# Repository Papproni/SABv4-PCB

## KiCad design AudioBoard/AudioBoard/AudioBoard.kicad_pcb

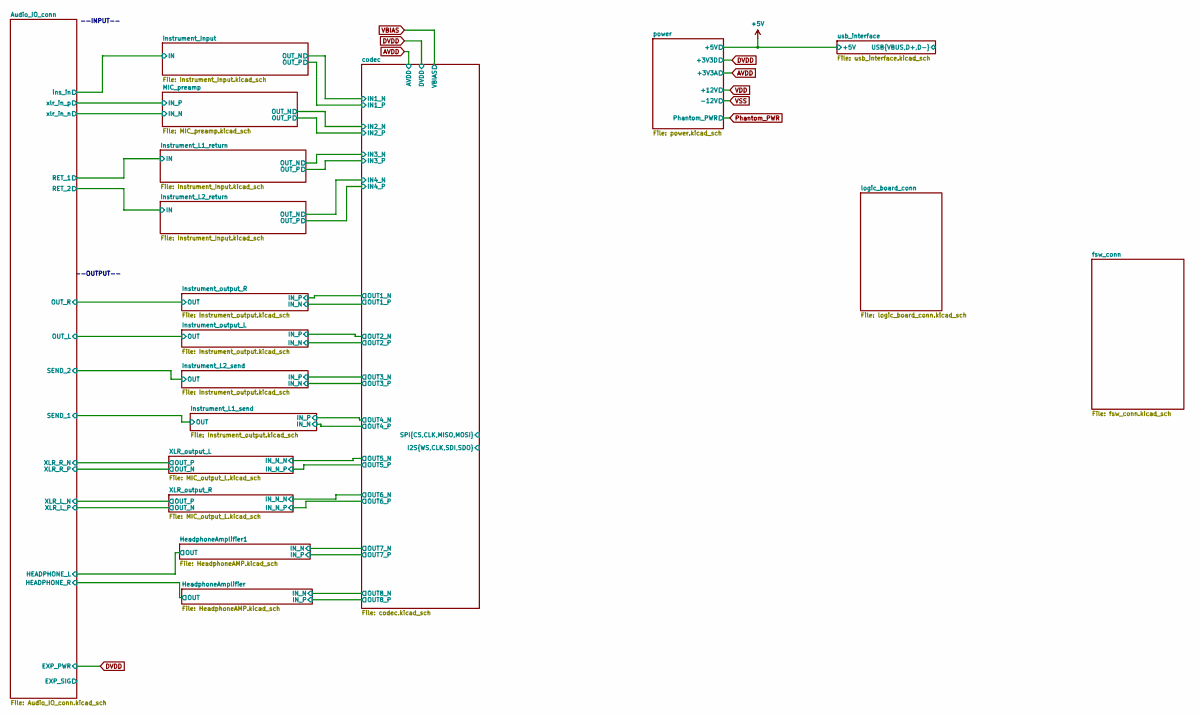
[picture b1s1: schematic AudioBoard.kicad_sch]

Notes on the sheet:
--OUTPUT--
--INPUT--

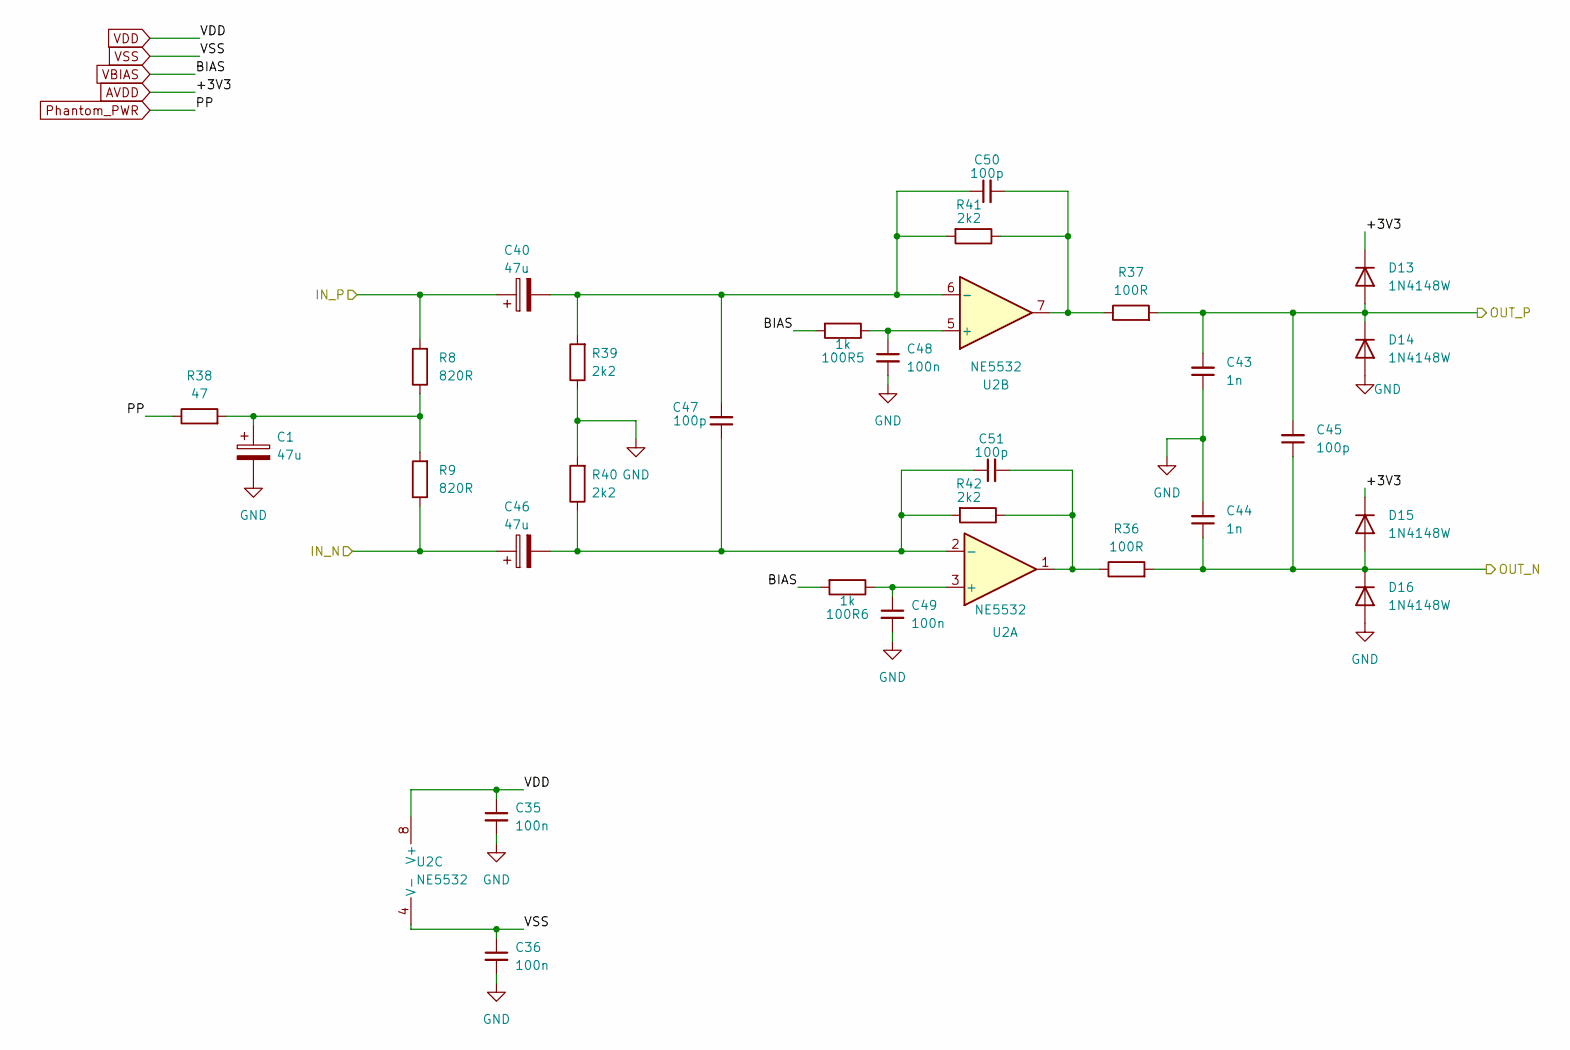
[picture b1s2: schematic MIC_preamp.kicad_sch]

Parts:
100R5, 100R6: 1k; R_0402_1005Metric; JLCPCB C11702
C1, C40, C46: 47u; CP_Radial_D6.3mm_P2.50mm; JLCPCB C45673
C35, C36, C48, C49: 100n; C_0402_1005Metric; JLCPCB C1591
C43, C44: 1n; C_0402_1005Metric; JLCPCB C1523
C45, C47, C50, C51: 100p; C_0402_1005Metric; JLCPCB C1546
D13, D14, D15, D16: 1N4148W; D_SOD-123; JLCPCB C81598
R8, R9: 820R; R_0603_1608Metric; JLCPCB C23253
R36, R37: 100R; R_0402_1005Metric; JLCPCB C25076
R38: 47; R_0603_1608Metric; JLCPCB C23182
R39, R40, R41, R42: 2k2; R_0402_1005Metric; JLCPCB C25879
U2: NE5532; SOIC-8_3.9x4.9mm_P1.27mm; JLCPCB C7426

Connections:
/Audio_IO_conn/xlr_in_n: C46.1, R9.1; also elsewhere on the board
/Audio_IO_conn/xlr_in_p: C40.1, R8.2; also elsewhere on the board
/MIC_preamp/OUT_N: C44.1, C45.1, D15.2 (A), D16.1 (K), R36.2; also elsewhere on the board
/MIC_preamp/OUT_P: C43.2, C45.2, D13.2 (A), D14.1 (K), R37.2; also elsewhere on the board
AVDD: D13.1 (K), D15.1 (K); also elsewhere on the board
GND: C1.2, C35.2, C36.2, C43.1, C44.2, C48.2, C49.2, D14.2 (A), D16.2 (A), R39.1, R40.2; also elsewhere on the board
unnamed: C1.1, R8.1, R9.2, R38.2
unnamed: C50.2, R37.1, R41.1, U2.7
unnamed: C51.2, R36.1, R42.1, U2.1
unnamed: 100R6.1, C49.1, U2.3 (+)
unnamed: C46.2, C47.1, C51.1, R40.1, R42.2, U2.2 (-)
unnamed: 100R5.1, C48.1, U2.5 (+)
unnamed: C40.2, C47.2, C50.1, R39.2, R41.2, U2.6 (-)
Phantom_PWR: R38.1; also elsewhere on the board
VBIAS: 100R5.2, 100R6.2; also elsewhere on the board
VDD: C35.1, U2.8 (V+); also elsewhere on the board
VSS: C36.1, U2.4 (V-); also elsewhere on the board

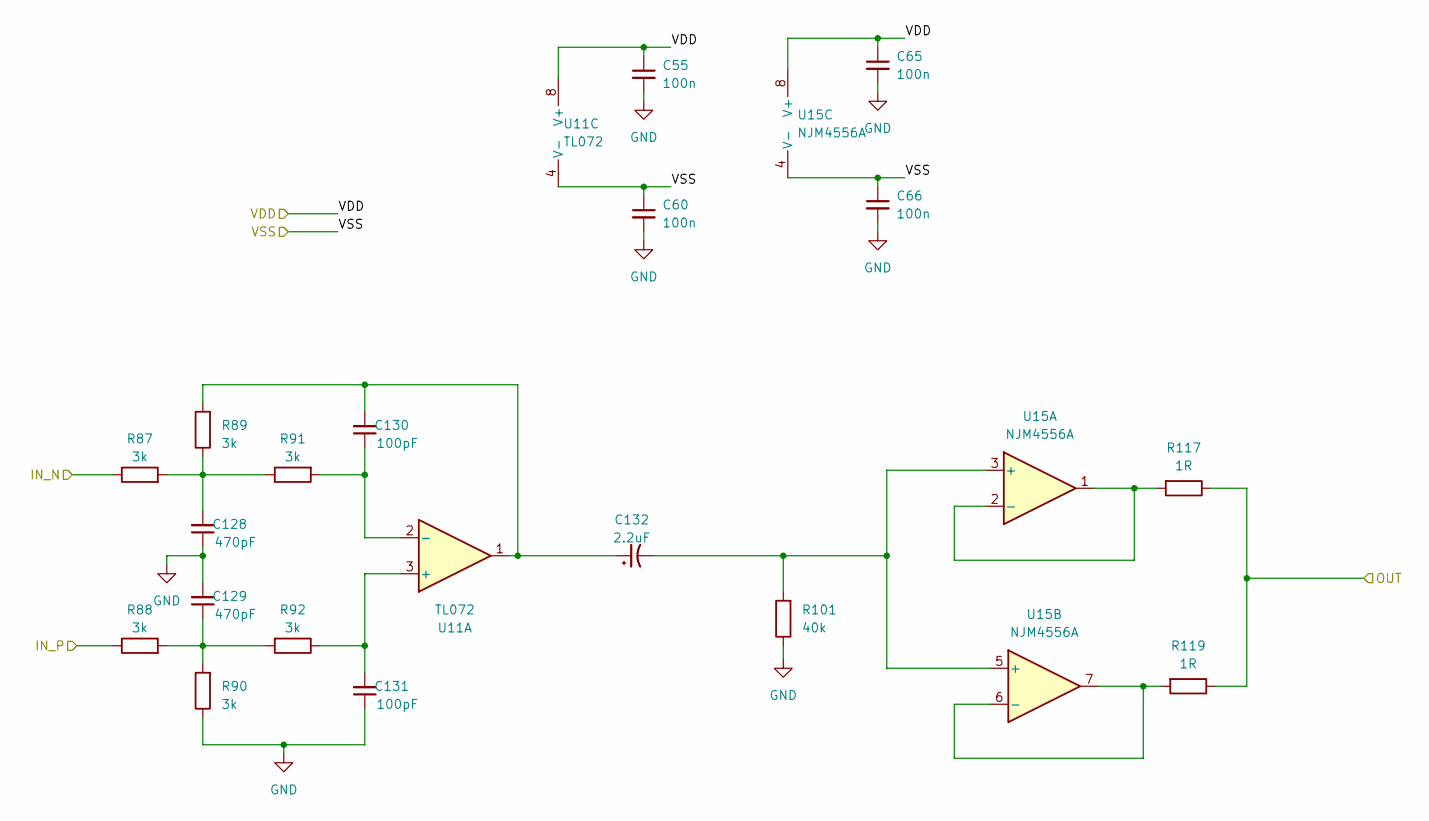
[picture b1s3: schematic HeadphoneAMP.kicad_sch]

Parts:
C55, C60, C65, C66: 100n; C_0402_1005Metric; JLCPCB C1591
C128, C129: 470pF; C_0603_1608Metric; JLCPCB C1620
C130, C131: 100pF; C_0603_1608Metric; JLCPCB C14858
C132: 2.2uF; C_0805_2012Metric_Pad1.18x1.45mm_HandSolder; JLCPCB C377773
R87, R88, R89, R90, R91, R92: 3k; R_0603_1608Metric; JLCPCB C4211
R101: 40k; R_0603_1608Metric; JLCPCB C21190
R117, R119: 1R; R_0603_1608Metric; JLCPCB C21190
U11: TL072; SOIC-8_3.9x4.9mm_P1.27mm; JLCPCB C6961
U15: NJM4556A; SOIC-8_5.3x5.3mm_P1.27mm; JLCPCB C3018893

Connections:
/Audio_IO_conn/HEADPHONE_R: R117.1, R119.1; also elsewhere on the board
/HeadphoneAmplifier/IN_N: R87.1; also elsewhere on the board
/HeadphoneAmplifier/IN_P: R88.1; also elsewhere on the board
/HeadphoneAmplifier/VDD: C55.1, C65.1, U11.8 (V+), U15.8 (V+)
/HeadphoneAmplifier/VSS: C60.1, C66.1, U11.4 (V-), U15.4 (V-)
GND: C55.2, C60.2, C65.2, C66.2, C128.1, C129.2, C131.1, R90.1, R101.1; also elsewhere on the board
unnamed: C128.2, R87.2, R89.1, R91.1
unnamed: C129.1, R88.2, R90.2, R92.2
unnamed: C130.2, C132.1, R89.2, U11.1
unnamed: C131.2, R92.1, U11.3 (+)
unnamed: C130.1, R91.2, U11.2 (-)
unnamed: C132.2, R101.2, U15.3 (+), U15.5 (+)
unnamed: R117.2, U15.1, U15.2 (-)
unnamed: R119.2, U15.6 (-), U15.7

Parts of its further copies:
C63, C64, C69, C70: 100n; C_0402_1005Metric; JLCPCB C1591
C133, C134: 470pF; C_0603_1608Metric; JLCPCB C1620
C135, C136: 100pF; C_0603_1608Metric; JLCPCB C14858
C137: 2.2uF; C_0805_2012Metric_Pad1.18x1.45mm_HandSolder; JLCPCB C377773
R94, R95, R96, R97, R98, R99: 3k; R_0603_1608Metric; JLCPCB C4211
R102: 40k; R_0603_1608Metric; JLCPCB C21190
R118, R120: 1R; R_0603_1608Metric; JLCPCB C21190
U14: TL072; SOIC-8_3.9x4.9mm_P1.27mm; JLCPCB C6961
U18: NJM4556A; SOIC-8_5.3x5.3mm_P1.27mm; JLCPCB C3018893

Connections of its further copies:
/Audio_IO_conn/HEADPHONE_L: R118.1, R120.1; also elsewhere on the board
/HeadphoneAmplifier1/IN_N: R94.1; also elsewhere on the board
/HeadphoneAmplifier1/IN_P: R95.1; also elsewhere on the board
/HeadphoneAmplifier1/VDD: C63.1, C69.1, U14.8 (V+), U18.8 (V+)
/HeadphoneAmplifier1/VSS: C64.1, C70.1, U14.4 (V-), U18.4 (V-)
GND: C63.2, C64.2, C69.2, C70.2, C133.1, C134.2, C136.1, R97.1, R102.1; also elsewhere on the board
unnamed: C133.2, R94.2, R96.1, R98.1
unnamed: C134.1, R95.2, R97.2, R99.2
unnamed: C135.2, C137.1, R96.2, U14.1
unnamed: C136.2, R99.1, U14.3 (+)
unnamed: C135.1, R98.2, U14.2 (-)
unnamed: C137.2, R102.2, U18.3 (+), U18.5 (+)
unnamed: R118.2, U18.1, U18.2 (-)
unnamed: R120.2, U18.6 (-), U18.7

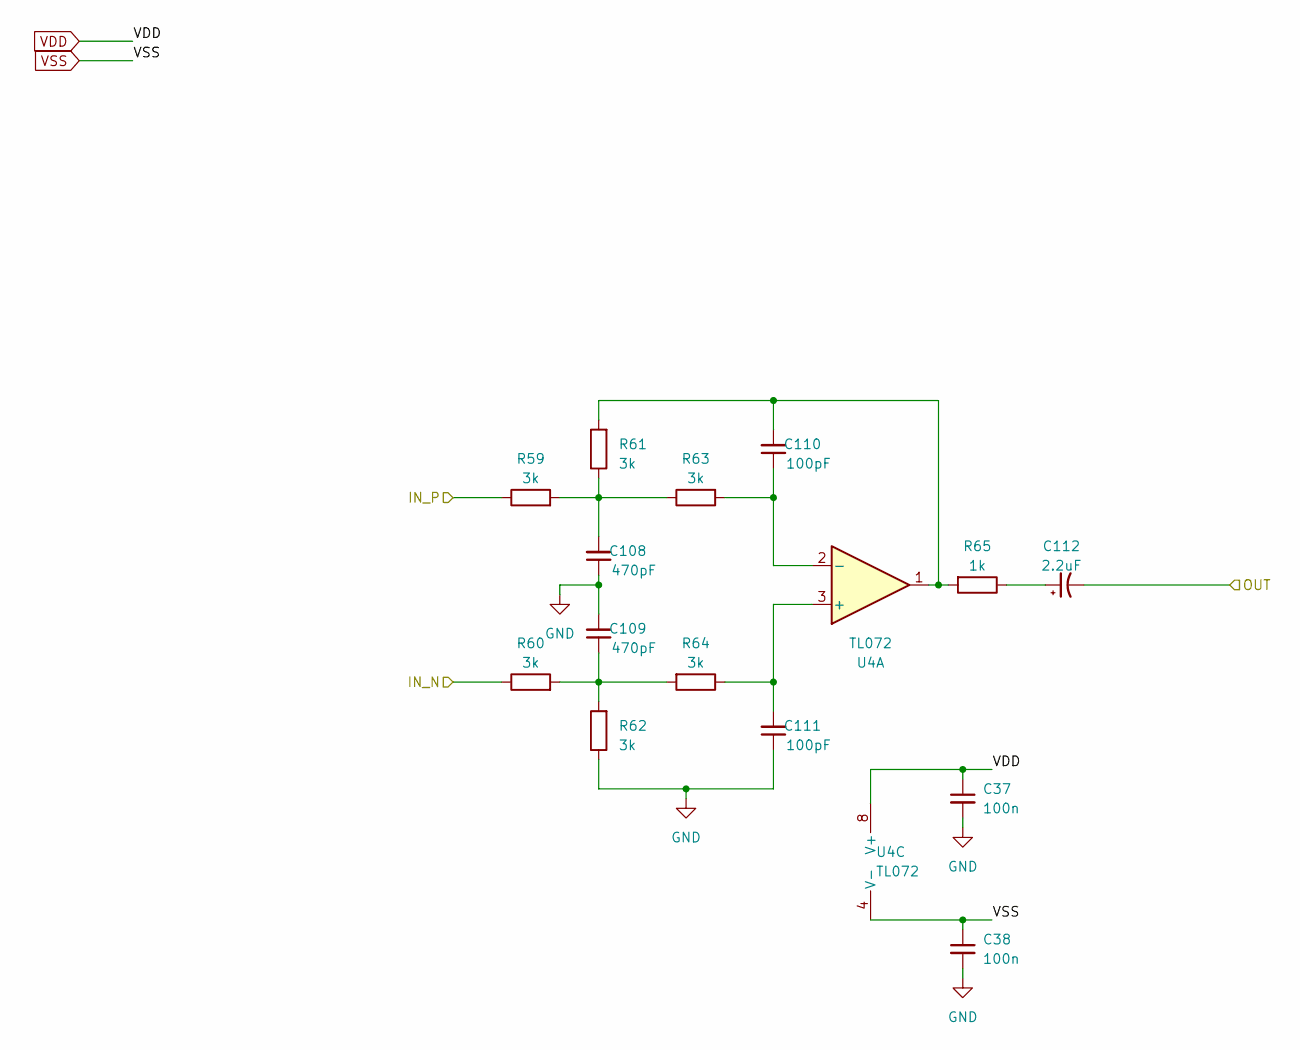
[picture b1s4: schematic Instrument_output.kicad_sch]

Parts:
C37, C38: 100n; C_0402_1005Metric; JLCPCB C1591
C108, C109: 470pF; C_0603_1608Metric; JLCPCB C1620
C110, C111: 100pF; C_0603_1608Metric; JLCPCB C14858
C112: 2.2uF; C_0805_2012Metric_Pad1.18x1.45mm_HandSolder; JLCPCB C377773
R59, R60, R61, R62, R63, R64: 3k; R_0603_1608Metric; JLCPCB C4211
R65: 1k; R_0603_1608Metric; JLCPCB C21190
U4: TL072; SOIC-8_3.9x4.9mm_P1.27mm; JLCPCB C6961

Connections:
/Audio_IO_conn/OUT_L: C112.2; also elsewhere on the board
/Instrument_output_L/IN_N: R60.1; also elsewhere on the board
/Instrument_output_L/IN_P: R59.1; also elsewhere on the board
GND: C37.2, C38.2, C108.1, C109.2, C111.1, R62.1; also elsewhere on the board
unnamed: C108.2, R59.2, R61.1, R63.1
unnamed: C109.1, R60.2, R62.2, R64.2
unnamed: C110.2, R61.2, R65.2, U4.1
unnamed: C112.1, R65.1
unnamed: C111.2, R64.1, U4.3 (+)
unnamed: C110.1, R63.2, U4.2 (-)
VDD: C37.1, U4.8 (V+); also elsewhere on the board
VSS: C38.1, U4.4 (V-); also elsewhere on the board

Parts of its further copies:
C39, C41, C42, C52, C53, C54: 100n; C_0402_1005Metric; JLCPCB C1591
C113, C114, C118, C119, C123, C124: 470pF; C_0603_1608Metric; JLCPCB C1620
C115, C116, C120, C121, C125, C126: 100pF; C_0603_1608Metric; JLCPCB C14858
C117, C122, C127: 2.2uF; C_0805_2012Metric_Pad1.18x1.45mm_HandSolder; JLCPCB C377773
R66, R67, R68, R69, R70, R71, R73, R74, R75, R76, R77, R78, R80, R81, R82, R83, R84, R85: 3k; R_0603_1608Metric; JLCPCB C4211
R72, R79, R86: 1k; R_0603_1608Metric; JLCPCB C21190
U8, U9, U10: TL072; SOIC-8_3.9x4.9mm_P1.27mm; JLCPCB C6961

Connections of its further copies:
/Audio_IO_conn/OUT_R: C117.2; also elsewhere on the board
/Audio_IO_conn/SEND_1: C122.2; also elsewhere on the board
/Audio_IO_conn/SEND_2: C127.2; also elsewhere on the board
/Instrument_L1_send/IN_N: R74.1; also elsewhere on the board
/Instrument_L1_send/IN_P: R73.1; also elsewhere on the board
/Instrument_L2_send/IN_N: R81.1; also elsewhere on the board
/Instrument_L2_send/IN_P: R80.1; also elsewhere on the board
/Instrument_output_R/IN_N: R67.1; also elsewhere on the board
/Instrument_output_R/IN_P: R66.1; also elsewhere on the board
GND: C39.2, C41.2, C42.2, C52.2, C53.2, C54.2, C113.1, C114.2, C116.1, C118.1, C119.2, C121.1, C123.1, C124.2, C126.1, R69.1, R76.1, R83.1; also elsewhere on the board
unnamed: C113.2, R66.2, R68.1, R70.1
unnamed: C114.1, R67.2, R69.2, R71.2
unnamed: C115.2, R68.2, R72.2, U8.1
unnamed: C117.1, R72.1
unnamed: C118.2, R73.2, R75.1, R77.1
unnamed: C119.1, R74.2, R76.2, R78.2
unnamed: C120.2, R75.2, R79.2, U9.1
unnamed: C122.1, R79.1
unnamed: C123.2, R80.2, R82.1, R84.1
unnamed: C124.1, R81.2, R83.2, R85.2
unnamed: C125.2, R82.2, R86.2, U10.1
unnamed: C127.1, R86.1
unnamed: C116.2, R71.1, U8.3 (+)
unnamed: C115.1, R70.2, U8.2 (-)
unnamed: C121.2, R78.1, U9.3 (+)
unnamed: C120.1, R77.2, U9.2 (-)
unnamed: C126.2, R85.1, U10.3 (+)
unnamed: C125.1, R84.2, U10.2 (-)
VDD: C39.1, C42.1, C53.1, U8.8 (V+), U9.8 (V+), U10.8 (V+); also elsewhere on the board
VSS: C41.1, C52.1, C54.1, U8.4 (V-), U9.4 (V-), U10.4 (V-); also elsewhere on the board

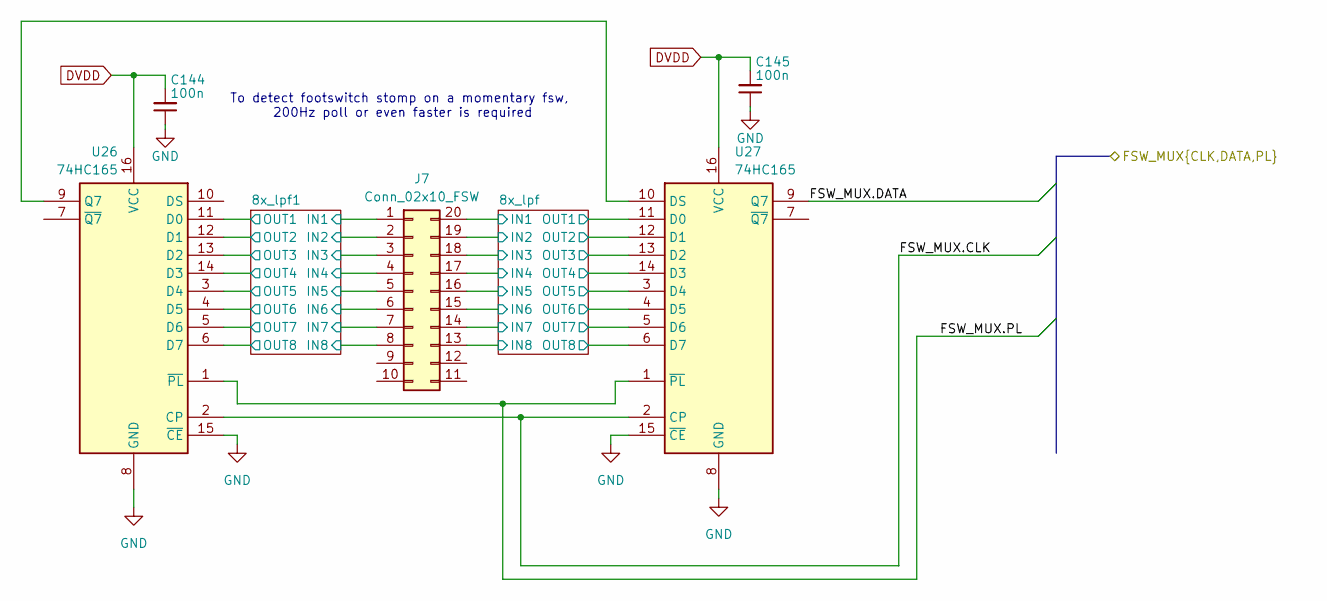
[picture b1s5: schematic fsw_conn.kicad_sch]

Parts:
C144, C145: 100n; C_0402_1005Metric; JLCPCB C1591
J7: Conn_02x10_FSW; PinSocket_2x10_P1.27mm_Vertical
U26, U27: 74HC165; SOIC-16_3.9x9.9mm_P1.27mm; LCSC part C5613

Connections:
/fsw_conn/8x_lpf1/IN1: U27.11 (D0); also elsewhere on the board
/fsw_conn/8x_lpf1/IN2: U27.12 (D1); also elsewhere on the board
/fsw_conn/8x_lpf1/IN3: U27.13 (D2); also elsewhere on the board
/fsw_conn/8x_lpf1/IN4: U27.14 (D3); also elsewhere on the board
/fsw_conn/8x_lpf1/IN5: U27.3 (D4); also elsewhere on the board
/fsw_conn/8x_lpf1/IN6: U27.4 (D5); also elsewhere on the board
/fsw_conn/8x_lpf1/IN7: U27.5 (D6); also elsewhere on the board
/fsw_conn/8x_lpf1/IN8: U27.6 (D7); also elsewhere on the board
/fsw_conn/8x_lpf1/OUT1: J7.20; also elsewhere on the board
/fsw_conn/8x_lpf1/OUT2: J7.19; also elsewhere on the board
/fsw_conn/8x_lpf1/OUT3: J7.18; also elsewhere on the board
/fsw_conn/8x_lpf1/OUT4: J7.17; also elsewhere on the board
/fsw_conn/8x_lpf1/OUT5: J7.16; also elsewhere on the board
/fsw_conn/8x_lpf1/OUT6: J7.15; also elsewhere on the board
/fsw_conn/8x_lpf1/OUT7: J7.14; also elsewhere on the board
/fsw_conn/8x_lpf1/OUT8: J7.13; also elsewhere on the board
/fsw_conn/8x_lpf/IN1: U26.11 (D0); also elsewhere on the board
/fsw_conn/8x_lpf/IN2: U26.12 (D1); also elsewhere on the board
/fsw_conn/8x_lpf/IN3: U26.13 (D2); also elsewhere on the board
/fsw_conn/8x_lpf/IN4: U26.14 (D3); also elsewhere on the board
/fsw_conn/8x_lpf/IN5: U26.3 (D4); also elsewhere on the board
/fsw_conn/8x_lpf/IN6: U26.4 (D5); also elsewhere on the board
/fsw_conn/8x_lpf/IN7: U26.5 (D6); also elsewhere on the board
/fsw_conn/8x_lpf/IN8: U26.6 (D7); also elsewhere on the board
/fsw_conn/8x_lpf/OUT1: J7.1; also elsewhere on the board
/fsw_conn/8x_lpf/OUT2: J7.2; also elsewhere on the board
/fsw_conn/8x_lpf/OUT3: J7.3; also elsewhere on the board
/fsw_conn/8x_lpf/OUT4: J7.4; also elsewhere on the board
/fsw_conn/8x_lpf/OUT5: J7.5; also elsewhere on the board
/fsw_conn/8x_lpf/OUT6: J7.6; also elsewhere on the board
/fsw_conn/8x_lpf/OUT7: J7.7; also elsewhere on the board
/fsw_conn/8x_lpf/OUT8: J7.8; also elsewhere on the board
/fsw_conn/FSW_MUX.CLK: U26.2 (CP), U27.2 (CP)
/fsw_conn/FSW_MUX.DATA: U27.9 (Q7)
/fsw_conn/FSW_MUX.PL: U26.1 (~PL), U27.1 (~PL)
DVDD: C144.2, C145.2, U26.16 (VCC), U27.16 (VCC); also elsewhere on the board
GND: C144.1, C145.1, U26.8 (GND), U26.15 (~CE), U27.8 (GND), U27.15 (~CE); also elsewhere on the board
unnamed: U26.9 (Q7), U27.10 (DS)

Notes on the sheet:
To detect footswitch stomp on a momentary fsw, 200Hz poll or even faster is required

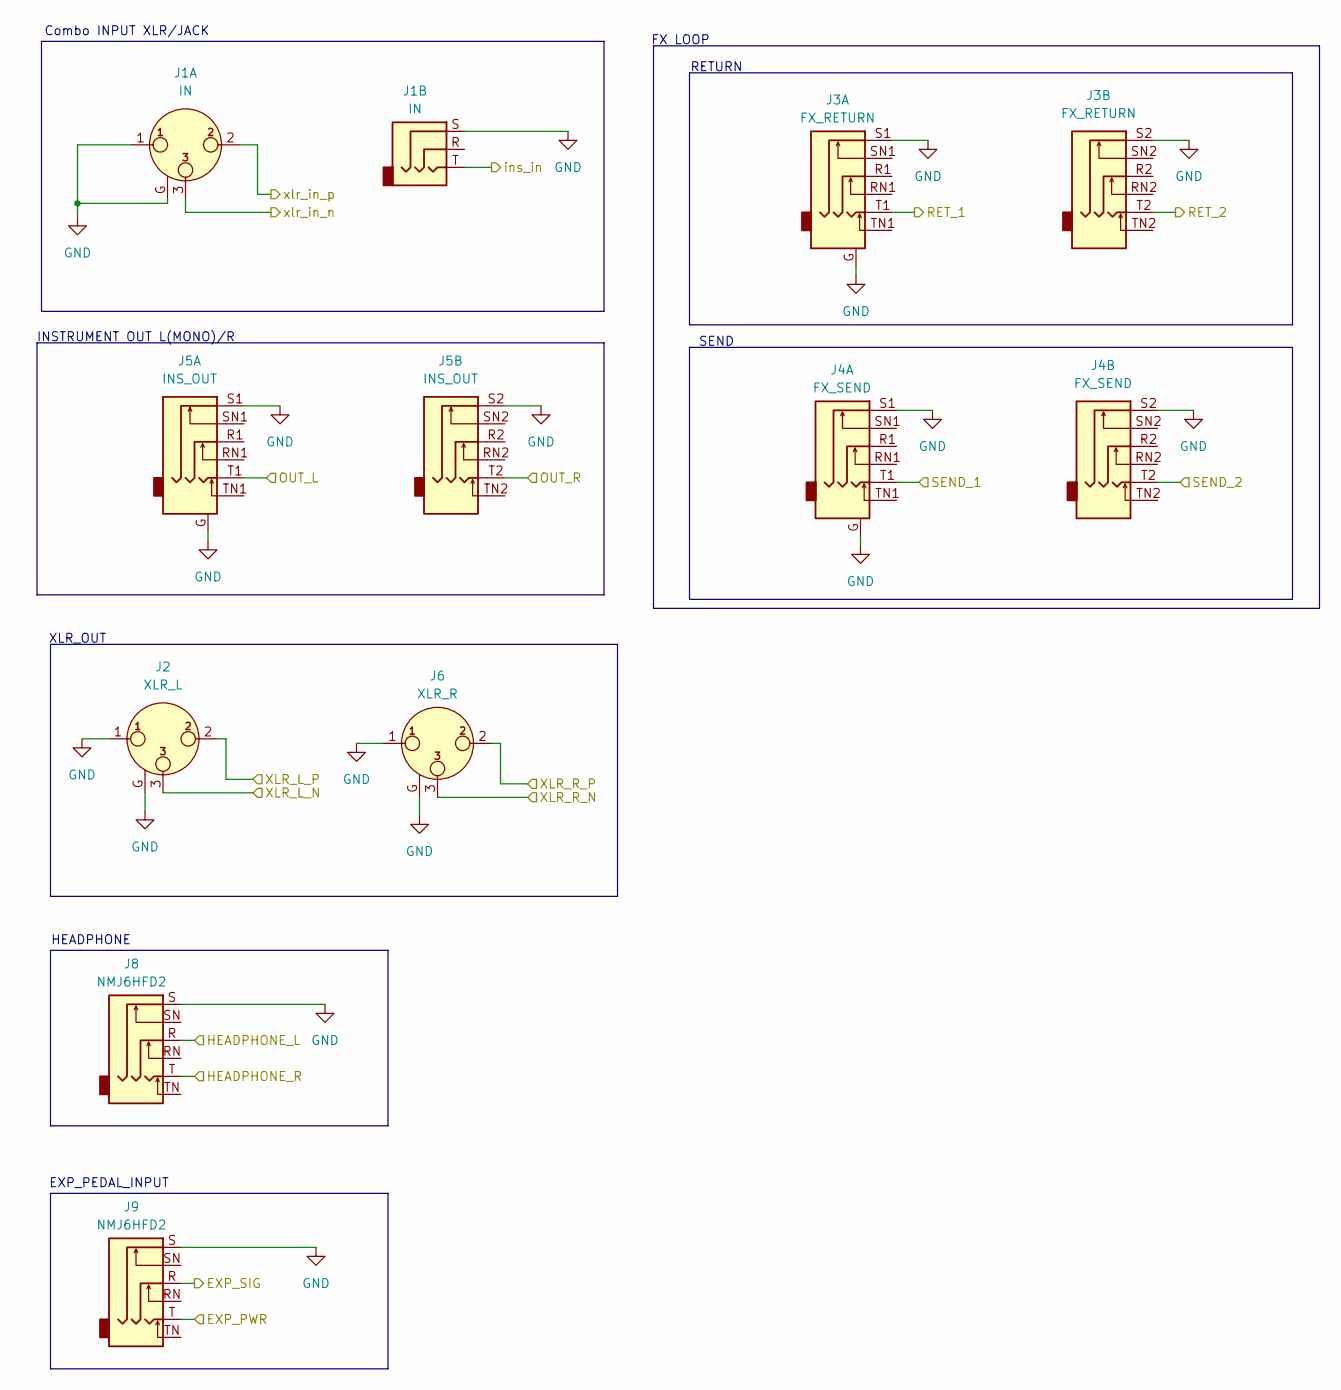
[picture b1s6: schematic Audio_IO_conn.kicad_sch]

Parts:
J1: IN; Jack_XLR-6.35mm_Neutrik_NCJ6FA-H_Horizontal; jlcpcbpart C368458
J2: XLR_L; Jack_XLR_Neutrik_NC3MAH_Horizontal; JLCPCB C23689430
J3: FX_RETURN; HAOYU_PJ-625; JLCPCB C309286
J4: FX_SEND; HAOYU_PJ-625; JLCPCB C309286
J5: INS_OUT; HAOYU_PJ-625; JLCPCB C309286
J6: XLR_R; Jack_XLR_Neutrik_NC3MAH_Horizontal; JLCPCB C23689430
J8, J9: NMJ6HFD2; Jack_6.35mm_Neutrik_NMJ6HFD2_Horizontal; JLCPCB C309279

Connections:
/Audio_IO_conn/EXP_SIG: J9.R
/Audio_IO_conn/HEADPHONE_L: J8.R; also elsewhere on the board
/Audio_IO_conn/HEADPHONE_R: J8.T; also elsewhere on the board
/Audio_IO_conn/OUT_L: J5.T1; also elsewhere on the board
/Audio_IO_conn/OUT_R: J5.T2; also elsewhere on the board
/Audio_IO_conn/RET_1: J3.T1; also elsewhere on the board
/Audio_IO_conn/RET_2: J3.T2; also elsewhere on the board
/Audio_IO_conn/SEND_1: J4.T1; also elsewhere on the board
/Audio_IO_conn/SEND_2: J4.T2; also elsewhere on the board
/Audio_IO_conn/XLR_L_N: J2.3; also elsewhere on the board
/Audio_IO_conn/XLR_L_P: J2.2; also elsewhere on the board
/Audio_IO_conn/XLR_R_N: J6.3; also elsewhere on the board
/Audio_IO_conn/XLR_R_P: J6.2; also elsewhere on the board
/Audio_IO_conn/ins_in: J1.T; also elsewhere on the board
/Audio_IO_conn/xlr_in_n: J1.3; also elsewhere on the board
/Audio_IO_conn/xlr_in_p: J1.2; also elsewhere on the board
DVDD: J9.T; also elsewhere on the board
GND: J1.1, J1.G, J1.S, J2.1, J2.G, J3.G, J3.S1, J3.S2, J4.G, J4.S1, J4.S2, J5.G, J5.S1, J5.S2, J6.1, J6.G, J8.S, J9.S; also elsewhere on the board

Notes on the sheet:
HEADPHONE
XLR_OUT
INSTRUMENT OUT L(MONO)/R
Combo INPUT XLR/JACK
RETURN
SEND
EXP_PEDAL_INPUT
FX LOOP

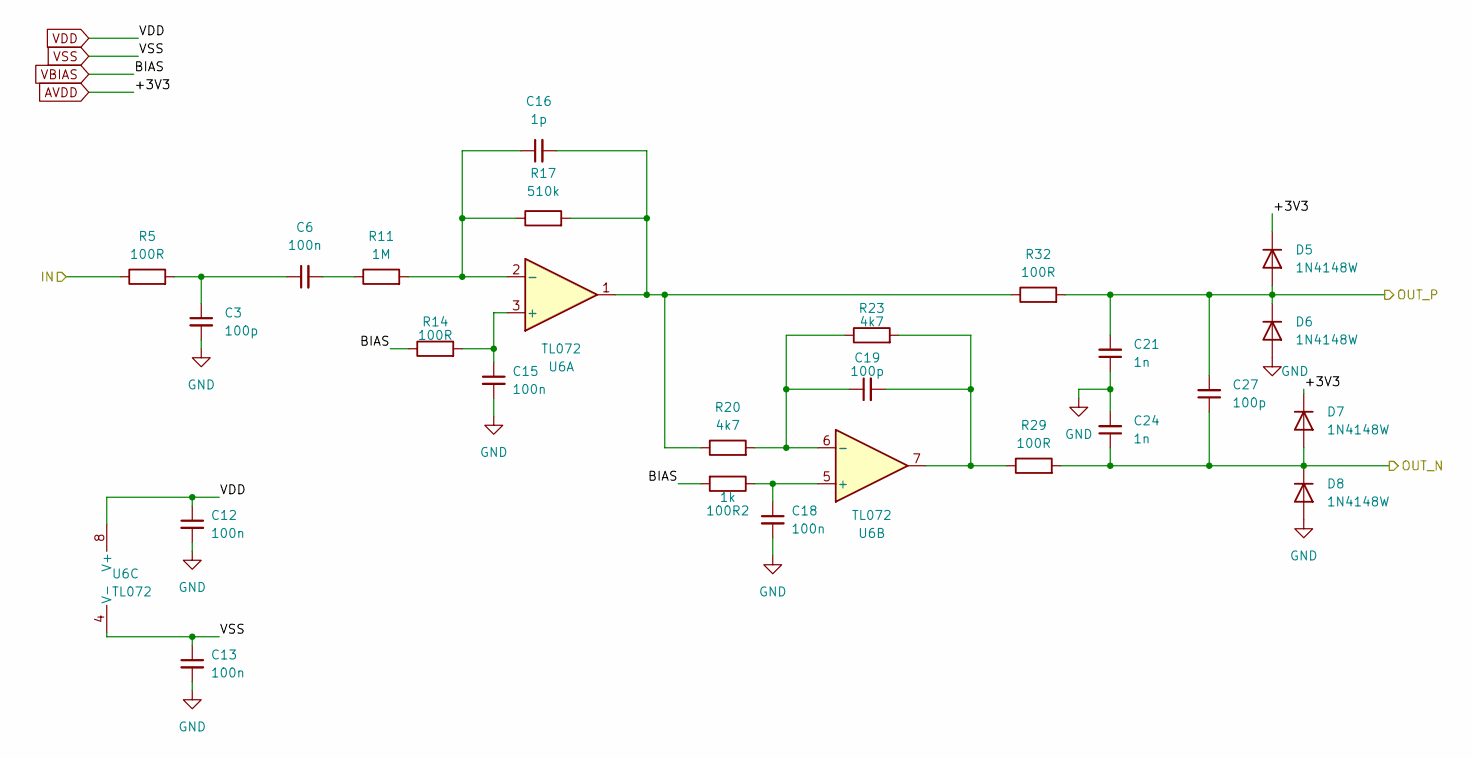
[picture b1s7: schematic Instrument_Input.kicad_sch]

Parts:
100R2: 1k; R_0402_1005Metric; JLCPCB C11702
C3, C19, C27: 100p; C_0402_1005Metric; JLCPCB C1546
C6, C12, C13, C15, C18: 100n; C_0402_1005Metric; JLCPCB C1591
C16: 1p; C_0402_1005Metric; JLCPCB C1550
C21, C24: 1n; C_0402_1005Metric; JLCPCB C1523
D5, D6, D7, D8: 1N4148W; D_SOD-123; JLCPCB C81598
R5, R14, R29, R32: 100R; R_0402_1005Metric; JLCPCB C25076
R11: 1M; R_0402_1005Metric; JLCPCB C26083
R17: 510k; R_0603_1608Metric; JLCPCB C23192
R20, R23: 4k7; R_0402_1005Metric; JLCPCB C25900
U6: TL072; SOIC-8_3.9x4.9mm_P1.27mm; JLCPCB C6961

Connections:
/Audio_IO_conn/RET_1: R5.1; also elsewhere on the board
/Instrument_L1_return/OUT_N: C24.1, C27.1, D7.2 (A), D8.1 (K), R29.2; also elsewhere on the board
/Instrument_L1_return/OUT_P: C21.2, C27.2, D5.2 (A), D6.1 (K), R32.2; also elsewhere on the board
AVDD: D5.1 (K), D7.1 (K); also elsewhere on the board
GND: C3.2, C12.2, C13.2, C15.2, C18.2, C21.1, C24.2, D6.2 (A), D8.2 (A); also elsewhere on the board
unnamed: C3.1, C6.1, R5.2
unnamed: C6.2, R11.1
unnamed: C16.2, R17.2, R20.1, R32.1, U6.1
unnamed: C19.2, R23.2, R29.1, U6.7
unnamed: C15.1, R14.2, U6.3 (+)
unnamed: C16.1, R11.2, R17.1, U6.2 (-)
unnamed: 100R2.1, C18.1, U6.5 (+)
unnamed: C19.1, R20.2, R23.1, U6.6 (-)
VBIAS: 100R2.2, R14.1; also elsewhere on the board
VDD: C12.1, U6.8 (V+); also elsewhere on the board
VSS: C13.1, U6.4 (V-); also elsewhere on the board

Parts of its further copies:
100R1, 100R3: 1k; R_0402_1005Metric; JLCPCB C11702
C2, C4, C14, C26, C31, C34: 100p; C_0402_1005Metric; JLCPCB C1546
C5, C7, C8, C9, C10, C17, C22, C25, C28, C30: 100n; C_0402_1005Metric; JLCPCB C1591
C11, C29: 1p; C_0402_1005Metric; JLCPCB C1550
C20, C23, C32, C33: 1n; C_0402_1005Metric; JLCPCB C1523
D1, D2, D3, D4, D9, D10, D11, D12: 1N4148W; D_SOD-123; JLCPCB C81598
R4, R6, R13, R15, R28, R30, R31, R33: 100R; R_0402_1005Metric; JLCPCB C25076
R10, R12: 1M; R_0402_1005Metric; JLCPCB C26083
R16, R18: 510k; R_0603_1608Metric; JLCPCB C23192
R19, R21, R22, R24: 4k7; R_0402_1005Metric; JLCPCB C25900
U5, U7: TL072; SOIC-8_3.9x4.9mm_P1.27mm; JLCPCB C6961

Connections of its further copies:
/Audio_IO_conn/RET_2: R6.1; also elsewhere on the board
/Audio_IO_conn/ins_in: R4.1; also elsewhere on the board
/Instrument_Input/OUT_N: C23.1, C26.1, D3.2 (A), D4.1 (K), R28.2; also elsewhere on the board
/Instrument_Input/OUT_P: C20.2, C26.2, D1.2 (A), D2.1 (K), R31.2; also elsewhere on the board
/Instrument_L2_return/OUT_N: C33.1, C34.1, D11.2 (A), D12.1 (K), R30.2; also elsewhere on the board
/Instrument_L2_return/OUT_P: C32.2, C34.2, D9.2 (A), D10.1 (K), R33.2; also elsewhere on the board
AVDD: D1.1 (K), D3.1 (K), D9.1 (K), D11.1 (K); also elsewhere on the board
GND: C2.2, C4.2, C8.2, C9.2, C10.2, C17.2, C20.1, C22.2, C23.2, C25.2, C28.2, C30.2, C32.1, C33.2, D2.2 (A), D4.2 (A), D10.2 (A), D12.2 (A); also elsewhere on the board
unnamed: C2.1, C5.1, R4.2
unnamed: C4.1, C7.1, R6.2
unnamed: C5.2, R10.1
unnamed: C7.2, R12.1
unnamed: C11.2, R16.2, R19.1, R31.1, U5.1
unnamed: C14.2, R22.2, R28.1, U5.7
unnamed: C29.2, R18.2, R21.1, R33.1, U7.1
unnamed: C31.2, R24.2, R30.1, U7.7
unnamed: C8.1, R13.2, U5.3 (+)
unnamed: C11.1, R10.2, R16.1, U5.2 (-)
unnamed: 100R1.1, C17.1, U5.5 (+)
unnamed: C14.1, R19.2, R22.1, U5.6 (-)
unnamed: C28.1, R15.2, U7.3 (+)
unnamed: C29.1, R12.2, R18.1, U7.2 (-)
unnamed: 100R3.1, C30.1, U7.5 (+)
unnamed: C31.1, R21.2, R24.1, U7.6 (-)
VBIAS: 100R1.2, 100R3.2, R13.1, R15.1; also elsewhere on the board
VDD: C9.1, C22.1, U5.8 (V+), U7.8 (V+); also elsewhere on the board
VSS: C10.1, C25.1, U5.4 (V-), U7.4 (V-); also elsewhere on the board

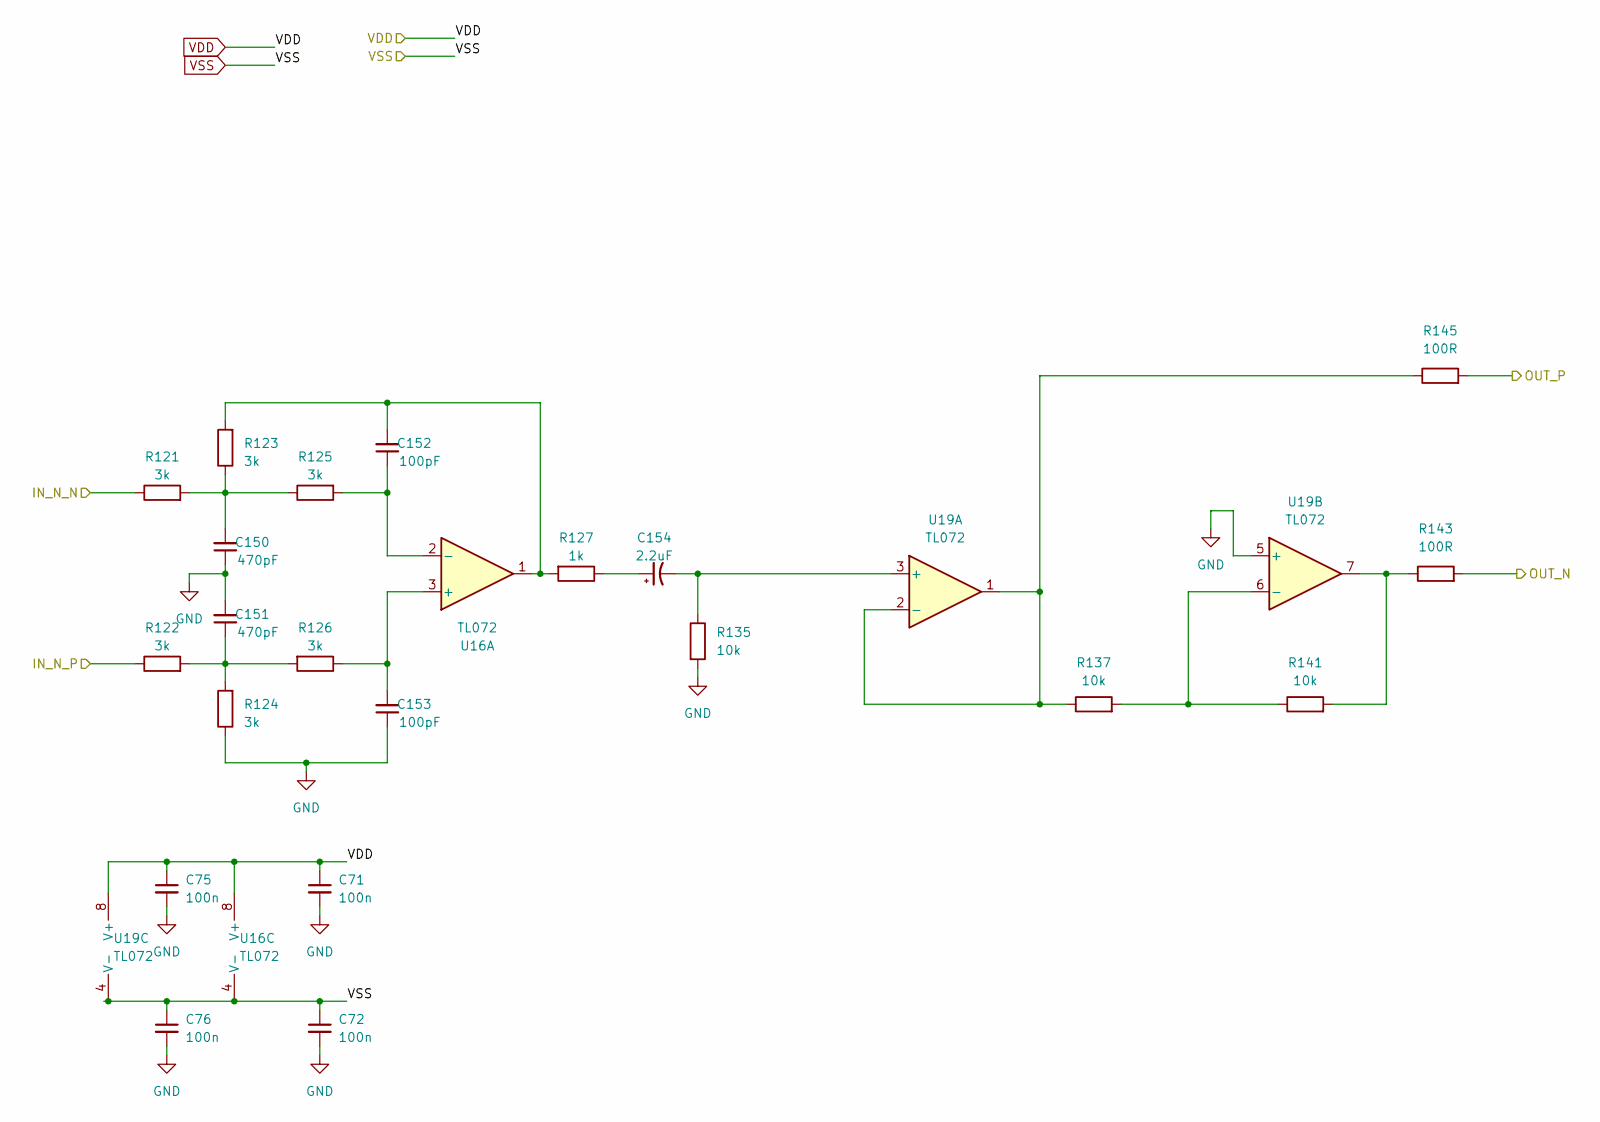
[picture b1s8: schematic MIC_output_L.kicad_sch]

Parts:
C71, C72, C75, C76: 100n; C_0402_1005Metric; JLCPCB C1591
C150, C151: 470pF; C_0603_1608Metric; JLCPCB C1620
C152, C153: 100pF; C_0603_1608Metric; JLCPCB C14858
C154: 2.2uF; C_0805_2012Metric_Pad1.18x1.45mm_HandSolder; JLCPCB C377773
R121, R122, R123, R124, R125, R126: 3k; R_0603_1608Metric; JLCPCB C4211
R127: 1k; R_0603_1608Metric; JLCPCB C21190
R135, R137, R141: 10k; R_0603_1608Metric; JLCPCB C4184
R143, R145: 100R; R_0402_1005Metric; JLCPCB C25076
U16, U19: TL072; SOIC-8_3.9x4.9mm_P1.27mm; JLCPCB C6961

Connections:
/Audio_IO_conn/XLR_R_N: R145.2; also elsewhere on the board
/Audio_IO_conn/XLR_R_P: R143.2; also elsewhere on the board
/XLR_output_L/IN_N_N: R121.1; also elsewhere on the board
/XLR_output_L/IN_N_P: R122.1; also elsewhere on the board
GND: C71.2, C72.2, C75.2, C76.2, C150.1, C151.2, C153.1, R124.1, R135.2, U19.5 (+); also elsewhere on the board
unnamed: C150.2, R121.2, R123.1, R125.1
unnamed: C151.1, R122.2, R124.2, R126.2
unnamed: C152.2, R123.2, R127.2, U16.1
unnamed: C154.1, R127.1
unnamed: R141.2, R143.1, U19.7
unnamed: C153.2, R126.1, U16.3 (+)
unnamed: C152.1, R125.2, U16.2 (-)
unnamed: C154.2, R135.1, U19.3 (+)
unnamed: R137.1, R145.1, U19.1, U19.2 (-)
unnamed: R137.2, R141.1, U19.6 (-)
VDD: C71.1, C75.1, U16.8 (V+), U19.8 (V+); also elsewhere on the board
VSS: C72.1, C76.1, U16.4 (V-), U19.4 (V-); also elsewhere on the board

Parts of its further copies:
C73, C74, C77, C78: 100n; C_0402_1005Metric; JLCPCB C1591
C155, C156: 470pF; C_0603_1608Metric; JLCPCB C1620
C157, C158: 100pF; C_0603_1608Metric; JLCPCB C14858
C159: 2.2uF; C_0805_2012Metric_Pad1.18x1.45mm_HandSolder; JLCPCB C377773
R128, R129, R130, R131, R132, R133: 3k; R_0603_1608Metric; JLCPCB C4211
R134: 1k; R_0603_1608Metric; JLCPCB C21190
R136, R138, R142: 10k; R_0603_1608Metric; JLCPCB C4184
R144, R146: 100R; R_0402_1005Metric; JLCPCB C25076
U17, U20: TL072; SOIC-8_3.9x4.9mm_P1.27mm; JLCPCB C6961

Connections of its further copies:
/Audio_IO_conn/XLR_L_N: R146.2; also elsewhere on the board
/Audio_IO_conn/XLR_L_P: R144.2; also elsewhere on the board
/XLR_output_R/IN_N_N: R128.1; also elsewhere on the board
/XLR_output_R/IN_N_P: R129.1; also elsewhere on the board
GND: C73.2, C74.2, C77.2, C78.2, C155.1, C156.2, C158.1, R131.1, R136.2, U20.5 (+); also elsewhere on the board
unnamed: C155.2, R128.2, R130.1, R132.1
unnamed: C156.1, R129.2, R131.2, R133.2
unnamed: C157.2, R130.2, R134.2, U17.1
unnamed: C159.1, R134.1
unnamed: R142.2, R144.1, U20.7
unnamed: C158.2, R133.1, U17.3 (+)
unnamed: C157.1, R132.2, U17.2 (-)
unnamed: C159.2, R136.1, U20.3 (+)
unnamed: R138.1, R146.1, U20.1, U20.2 (-)
unnamed: R138.2, R142.1, U20.6 (-)
VDD: C73.1, C77.1, U17.8 (V+), U20.8 (V+); also elsewhere on the board
VSS: C74.1, C78.1, U17.4 (V-), U20.4 (V-); also elsewhere on the board

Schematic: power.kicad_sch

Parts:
J7_PWR_IN1: HC-DC-005-2.0T; BarrelJack_Wuerth_6941xx301002; jlcpcbpart C3010533
R52: 100k; R_0402_1005Metric; JLCPCB C25741
R53: 20k; R_0603_1608Metric; JLCPCB C4184
R54: 0R; R_0603_1608Metric_Pad0.98x0.95mm_HandSolder; JLCPCB C21189; not fitted
SW3_pwr1: SS-12D28G7; jlcpcbpart C2884748

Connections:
/power/AnalogPower/EN: R54.1; also elsewhere on the board
/power/input_pwr_protection/VIN: J7_PWR_IN1.2, R52.1; also elsewhere on the board
/power/input_pwr_protection/\SHDN: R54.2, SW3_pwr1.3 (A); also elsewhere on the board
GNDPWR: J7_PWR_IN1.1, R53.2; also elsewhere on the board
unnamed: R52.2, R53.1, SW3_pwr1.2 (B)

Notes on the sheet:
If SHDN cirucit doesnt work
Center Negative wiring
DCDC modules EN: Float - Active GND - Inactive
PWR SPECS Voltage: +15-33 V Current: 0.5-2A

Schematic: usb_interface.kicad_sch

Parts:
C102: 100nF; C_0603_1608Metric; JLCPCB C14663
J11: USB_C_Receptacle_USB2.0; USB_C_Receptacle_XKB_U262-16XN-4BVC11; LCSC Part C393939
U23: USBLC6-2P6; SOT-666; JLCPCB C15999

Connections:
+5V: C102.1, U23.5 (VBUS); also elsewhere on the board
/usb_interface/USB.D+: U23.4 (I/O2)
/usb_interface/USB.D-: U23.6 (I/O1)
/usb_interface/USB.VBUS: J11.A4 (VBUS), J11.A9 (VBUS), J11.B4 (VBUS), J11.B9 (VBUS)
/usb_interface/USB_Conn_D+: J11.A6 (D+), J11.B6 (D+), U23.3 (I/O2)
/usb_interface/USB_Conn_D-: J11.A7 (D-), J11.B7 (D-), U23.1 (I/O1)
GND: C102.2, J11.A1 (GND), J11.A12 (GND), J11.B1 (GND), J11.B12 (GND), U23.2 (GND); also elsewhere on the board
